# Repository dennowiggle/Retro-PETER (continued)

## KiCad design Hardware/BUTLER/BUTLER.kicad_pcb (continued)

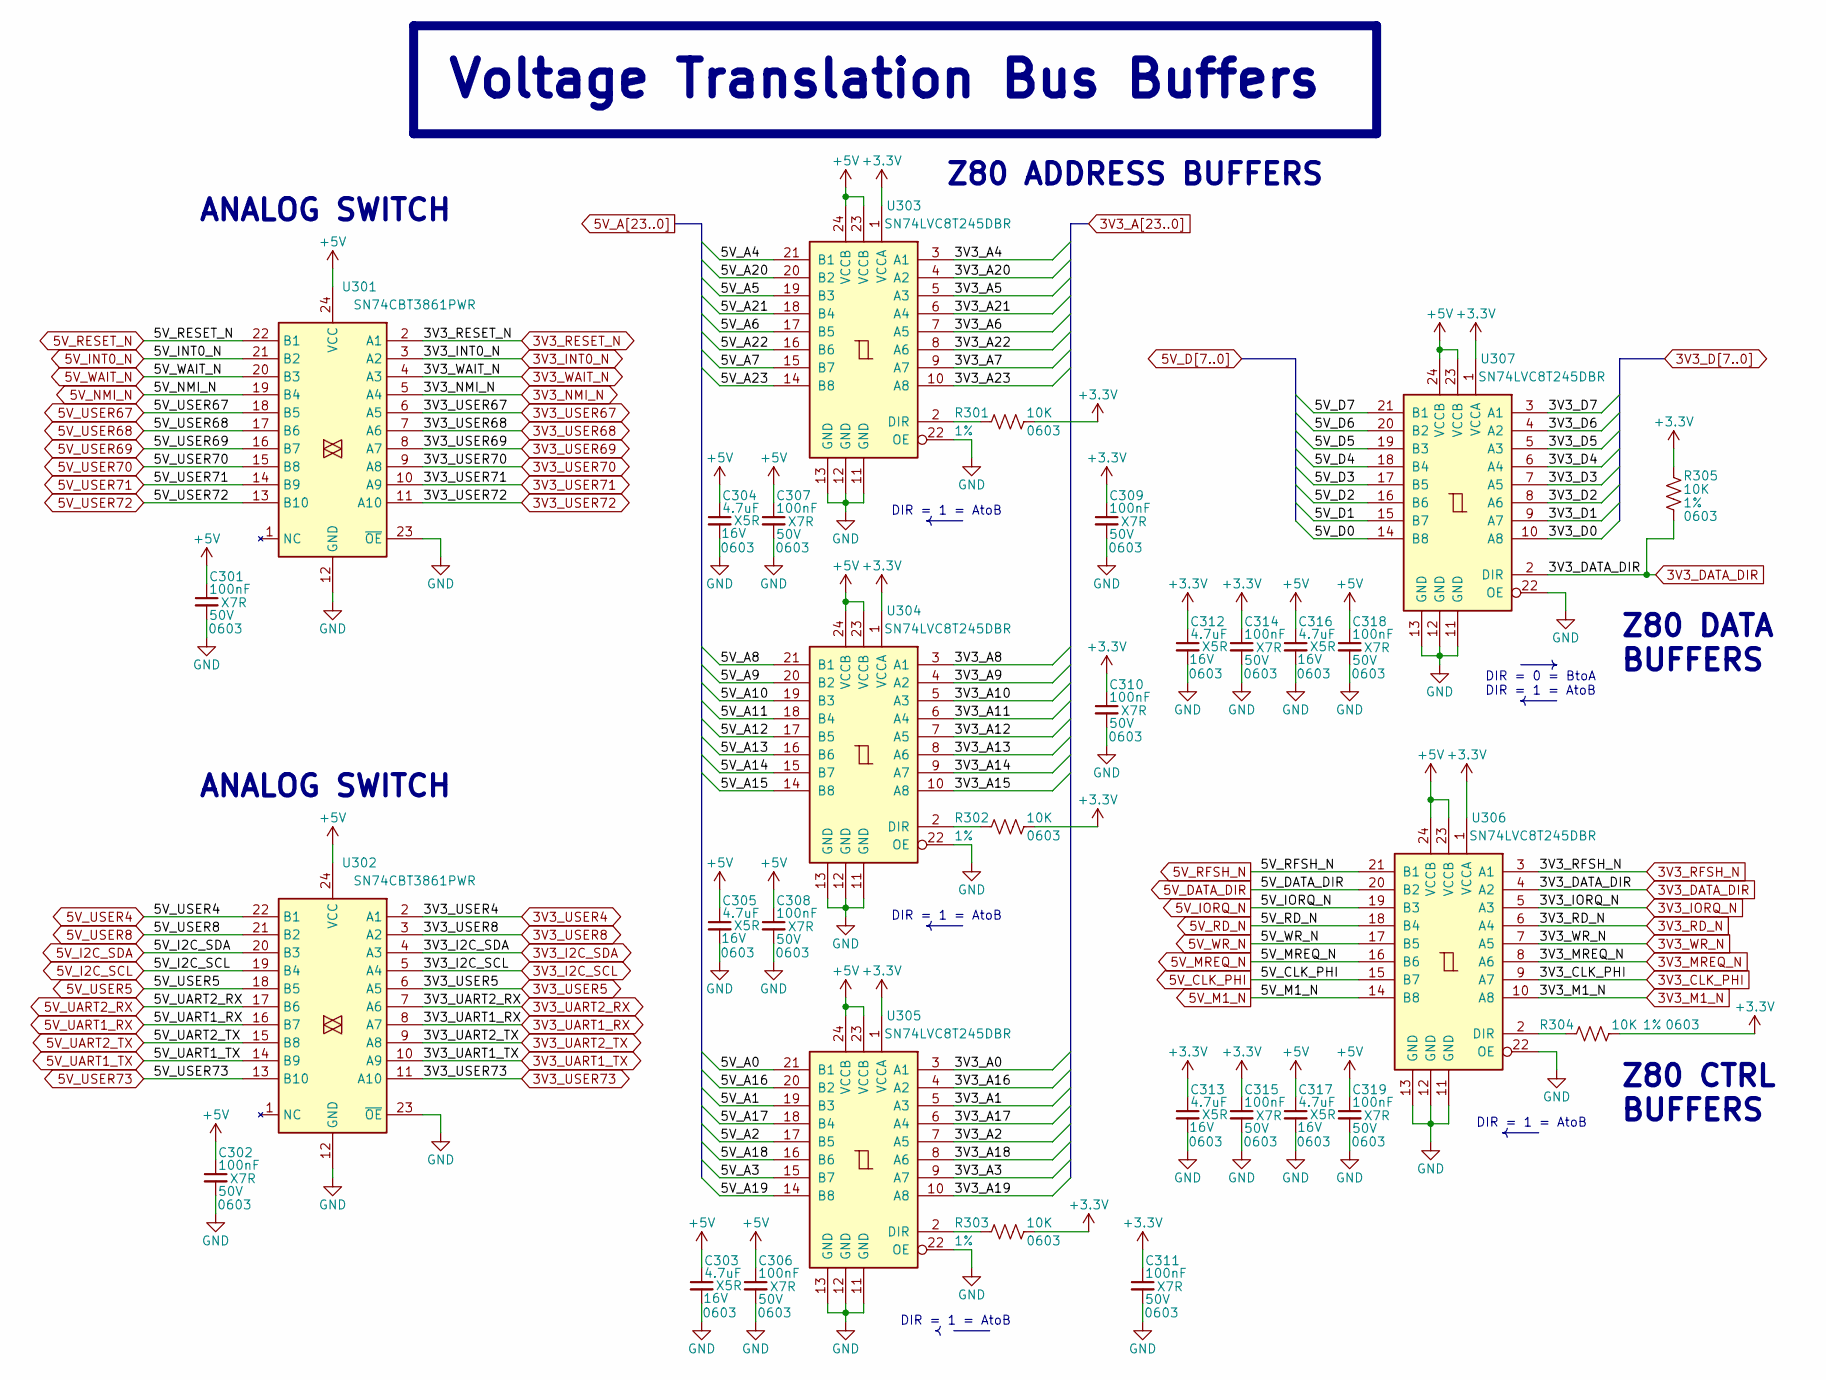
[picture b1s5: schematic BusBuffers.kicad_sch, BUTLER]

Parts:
C301, C302, C306, C307, C308, C309, C310, C311, C314, C315, C318, C319: 100nF; C_0603_1608Metric; Voltage 50V; Tolerance 10%; MPN CC0603KRX7R9BB104; Digikey 311-1344-1-ND
C303, C304, C305, C312, C313, C316, C317: 4.7uF; C_0603_1608Metric; Voltage 16V; Tolerance 10%; MPN CL10A475KO8NNNC; Digikey 1276-1784-1-ND
R301, R302, R303, R304, R305: 10K; R_0603_1608Metric; Tolerance 1%; MPN RC0603FR-0710KL; Digikey 311-10.0KHRCT-ND
U301, U302: SN74CBT3861PWR; TSSOP-24_4.4x7.8mm_P0.65mm; MPN SN74CBTD3861DBQR; Digikey 296-6483-1-ND
U303, U304, U305, U306, U307: SN74LVC8T245DBR; SSOP-24_5.3x8.2mm_P0.65mm; MPN SN74LVC8T245DBR; Digikey 296-21065-1-ND

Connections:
3V3_A0: U305.3 (A1); also elsewhere on the board
3V3_A1: U305.5 (A3); also elsewhere on the board
3V3_A2: U305.7 (A5); also elsewhere on the board
3V3_A3: U305.9 (A7); also elsewhere on the board
3V3_A4: U303.3 (A1); also elsewhere on the board
3V3_A5: U303.5 (A3); also elsewhere on the board
3V3_A6: U303.7 (A5); also elsewhere on the board
3V3_A7: U303.9 (A7); also elsewhere on the board
3V3_A8: U304.3 (A1); also elsewhere on the board
3V3_A9: U304.4 (A2); also elsewhere on the board
3V3_A10: U304.5 (A3); also elsewhere on the board
3V3_A11: U304.6 (A4); also elsewhere on the board
3V3_A12: U304.7 (A5); also elsewhere on the board
3V3_A13: U304.8 (A6); also elsewhere on the board
3V3_A14: U304.9 (A7); also elsewhere on the board
3V3_A15: U304.10 (A8); also elsewhere on the board
3V3_A16: U305.4 (A2); also elsewhere on the board
3V3_A17: U305.6 (A4); also elsewhere on the board
3V3_A18: U305.8 (A6); also elsewhere on the board
3V3_A19: U305.10 (A8); also elsewhere on the board
3V3_A20: U303.4 (A2); also elsewhere on the board
3V3_A21: U303.6 (A4); also elsewhere on the board
3V3_A22: U303.8 (A6); also elsewhere on the board
3V3_A23: U303.10 (A8); also elsewhere on the board
3V3_CLK_PHI: U306.9 (A7); also elsewhere on the board
3V3_D0: U307.10 (A8); also elsewhere on the board
3V3_D1: U307.9 (A7); also elsewhere on the board
3V3_D2: U307.8 (A6); also elsewhere on the board
3V3_D3: U307.7 (A5); also elsewhere on the board
3V3_D4: U307.6 (A4); also elsewhere on the board
3V3_D5: U307.5 (A3); also elsewhere on the board
3V3_D6: U307.4 (A2); also elsewhere on the board
3V3_D7: U307.3 (A1); also elsewhere on the board
3V3_DATA_DIR: R305.2, U306.4 (A2), U307.2 (DIR); also elsewhere on the board
3V3_I2C_SCL: U302.5 (A4); also elsewhere on the board
3V3_I2C_SDA: U302.4 (A3); also elsewhere on the board
3V3_INT0_N: U301.3 (A2); also elsewhere on the board
3V3_IORQ_N: U306.5 (A3); also elsewhere on the board
3V3_M1_N: U306.10 (A8); also elsewhere on the board
3V3_MREQ_N: U306.8 (A6); also elsewhere on the board
3V3_NMI_N: U301.5 (A4); also elsewhere on the board
3V3_RD_N: U306.6 (A4); also elsewhere on the board
3V3_RESET_N: U301.2 (A1); also elsewhere on the board
3V3_RFSH_N: U306.3 (A1); also elsewhere on the board
3V3_UART1_RX: U302.8 (A7); also elsewhere on the board
3V3_UART1_TX: U302.10 (A9); also elsewhere on the board
3V3_UART2_RX: U302.7 (A6); also elsewhere on the board
3V3_UART2_TX: U302.9 (A8); also elsewhere on the board
3V3_USER4: U302.2 (A1); also elsewhere on the board
3V3_USER5: U302.6 (A5); also elsewhere on the board
3V3_USER8: U302.3 (A2); also elsewhere on the board
3V3_USER67: U301.6 (A5); also elsewhere on the board
3V3_USER68: U301.7 (A6); also elsewhere on the board
3V3_USER69: U301.8 (A7); also elsewhere on the board
3V3_USER70: U301.9 (A8); also elsewhere on the board
3V3_USER71: U301.10 (A9); also elsewhere on the board
3V3_USER72: U301.11 (A10); also elsewhere on the board
3V3_USER73: U302.11 (A10); also elsewhere on the board
3V3_WAIT_N: U301.4 (A3); also elsewhere on the board
3V3_WR_N: U306.7 (A5); also elsewhere on the board
5V_A0: U305.21 (B1); also elsewhere on the board
5V_A1: U305.19 (B3); also elsewhere on the board
5V_A2: U305.17 (B5); also elsewhere on the board
5V_A3: U305.15 (B7); also elsewhere on the board
5V_A4: U303.21 (B1); also elsewhere on the board
5V_A5: U303.19 (B3); also elsewhere on the board
5V_A6: U303.17 (B5); also elsewhere on the board
5V_A7: U303.15 (B7); also elsewhere on the board
5V_A8: U304.21 (B1); also elsewhere on the board
5V_A9: U304.20 (B2); also elsewhere on the board
5V_A10: U304.19 (B3); also elsewhere on the board
5V_A11: U304.18 (B4); also elsewhere on the board
5V_A12: U304.17 (B5); also elsewhere on the board
5V_A13: U304.16 (B6); also elsewhere on the board
5V_A14: U304.15 (B7); also elsewhere on the board
5V_A15: U304.14 (B8); also elsewhere on the board
5V_A16: U305.20 (B2); also elsewhere on the board
5V_A17: U305.18 (B4); also elsewhere on the board
5V_A18: U305.16 (B6); also elsewhere on the board
5V_A19: U305.14 (B8); also elsewhere on the board
5V_A20: U303.20 (B2); also elsewhere on the board
5V_A21: U303.18 (B4); also elsewhere on the board
5V_A22: U303.16 (B6); also elsewhere on the board
5V_A23: U303.14 (B8); also elsewhere on the board
5V_CLK_PHI: U306.15 (B7); also elsewhere on the board
5V_D0: U307.14 (B8); also elsewhere on the board
5V_D1: U307.15 (B7); also elsewhere on the board
5V_D2: U307.16 (B6); also elsewhere on the board
5V_D3: U307.17 (B5); also elsewhere on the board
5V_D4: U307.18 (B4); also elsewhere on the board
5V_D5: U307.19 (B3); also elsewhere on the board
5V_D6: U307.20 (B2); also elsewhere on the board
5V_D7: U307.21 (B1); also elsewhere on the board
5V_DATA_DIR: U306.20 (B2); also elsewhere on the board
5V_I2C_SCL: U302.19 (B4); also elsewhere on the board
5V_I2C_SDA: U302.20 (B3); also elsewhere on the board
5V_INT0_N: U301.21 (B2); also elsewhere on the board
5V_IORQ_N: U306.19 (B3); also elsewhere on the board
5V_M1_N: U306.14 (B8); also elsewhere on the board
5V_MREQ_N: U306.16 (B6); also elsewhere on the board
5V_NMI_N: U301.19 (B4); also elsewhere on the board
5V_RD_N: U306.18 (B4); also elsewhere on the board
5V_RESET_N: U301.22 (B1); also elsewhere on the board
5V_RFSH_N: U306.21 (B1); also elsewhere on the board
5V_UART1_RX: U302.16 (B7); also elsewhere on the board
5V_UART1_TX: U302.14 (B9); also elsewhere on the board
5V_UART2_RX: U302.17 (B6); also elsewhere on the board
5V_UART2_TX: U302.15 (B8); also elsewhere on the board
5V_USER4: U302.22 (B1); also elsewhere on the board
5V_USER5: U302.18 (B5); also elsewhere on the board
5V_USER8: U302.21 (B2); also elsewhere on the board
5V_USER67: U301.18 (B5); also elsewhere on the board
5V_USER68: U301.17 (B6); also elsewhere on the board
5V_USER69: U301.16 (B7); also elsewhere on the board
5V_USER70: U301.15 (B8); also elsewhere on the board
5V_USER71: U301.14 (B9); also elsewhere on the board
5V_USER72: U301.13 (B10); also elsewhere on the board
5V_USER73: U302.13 (B10); also elsewhere on the board
5V_WAIT_N: U301.20 (B3); also elsewhere on the board
5V_WR_N: U306.17 (B5); also elsewhere on the board
+3.3V: C309.1, C310.1, C311.1, C312.1, C313.1, C314.1, C315.1, R301.2, R302.2, R303.2, R304.2, R305.1, U303.1 (VCCA), U304.1 (VCCA), U305.1 (VCCA), U306.1 (VCCA), U307.1 (VCCA); also elsewhere on the board
+5V: C301.1, C302.1, C303.1, C304.1, C305.1, C306.1, C307.1, C308.1, C316.1, C317.1, C318.1, C319.1, U301.24 (VCC), U302.24 (VCC), U303.23 (VCCB), U303.24 (VCCB), U304.23 (VCCB), U304.24 (VCCB), U305.23 (VCCB), U305.24 (VCCB), U306.23 (VCCB), U306.24 (VCCB), U307.23 (VCCB), U307.24 (VCCB); also elsewhere on the board
GND: C301.2, C302.2, C303.2, C304.2, C305.2, C306.2, C307.2, C308.2, C309.2, C310.2, C311.2, C312.2, C313.2, C314.2, C315.2, C316.2, C317.2, C318.2, C319.2, U301.12 (GND), U301.23 (~OE), U302.12 (GND), U302.23 (~OE), U303.11 (GND), U303.12 (GND), U303.13 (GND), U303.22 (OE), U304.11 (GND), U304.12 (GND), U304.13 (GND), U304.22 (OE), U305.11 (GND), U305.12 (GND), U305.13 (GND), U305.22 (OE), U306.11 (GND), U306.12 (GND), U306.13 (GND), U306.22 (OE), U307.11 (GND), U307.12 (GND), U307.13 (GND), U307.22 (OE); also elsewhere on the board
unnamed: R301.1, U303.2 (DIR)
unnamed: R302.1, U304.2 (DIR)
unnamed: R303.1, U305.2 (DIR)
unnamed: R304.1, U306.2 (DIR)

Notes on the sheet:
DIR = 1 = AtoB
DIR = 0 = BtoA
Z80 DATA BUFFERS
ANALOG SWITCH
Z80 ADDRESS BUFFERS
Z80 CTRL BUFFERS
Voltage Translation Bus Buffers

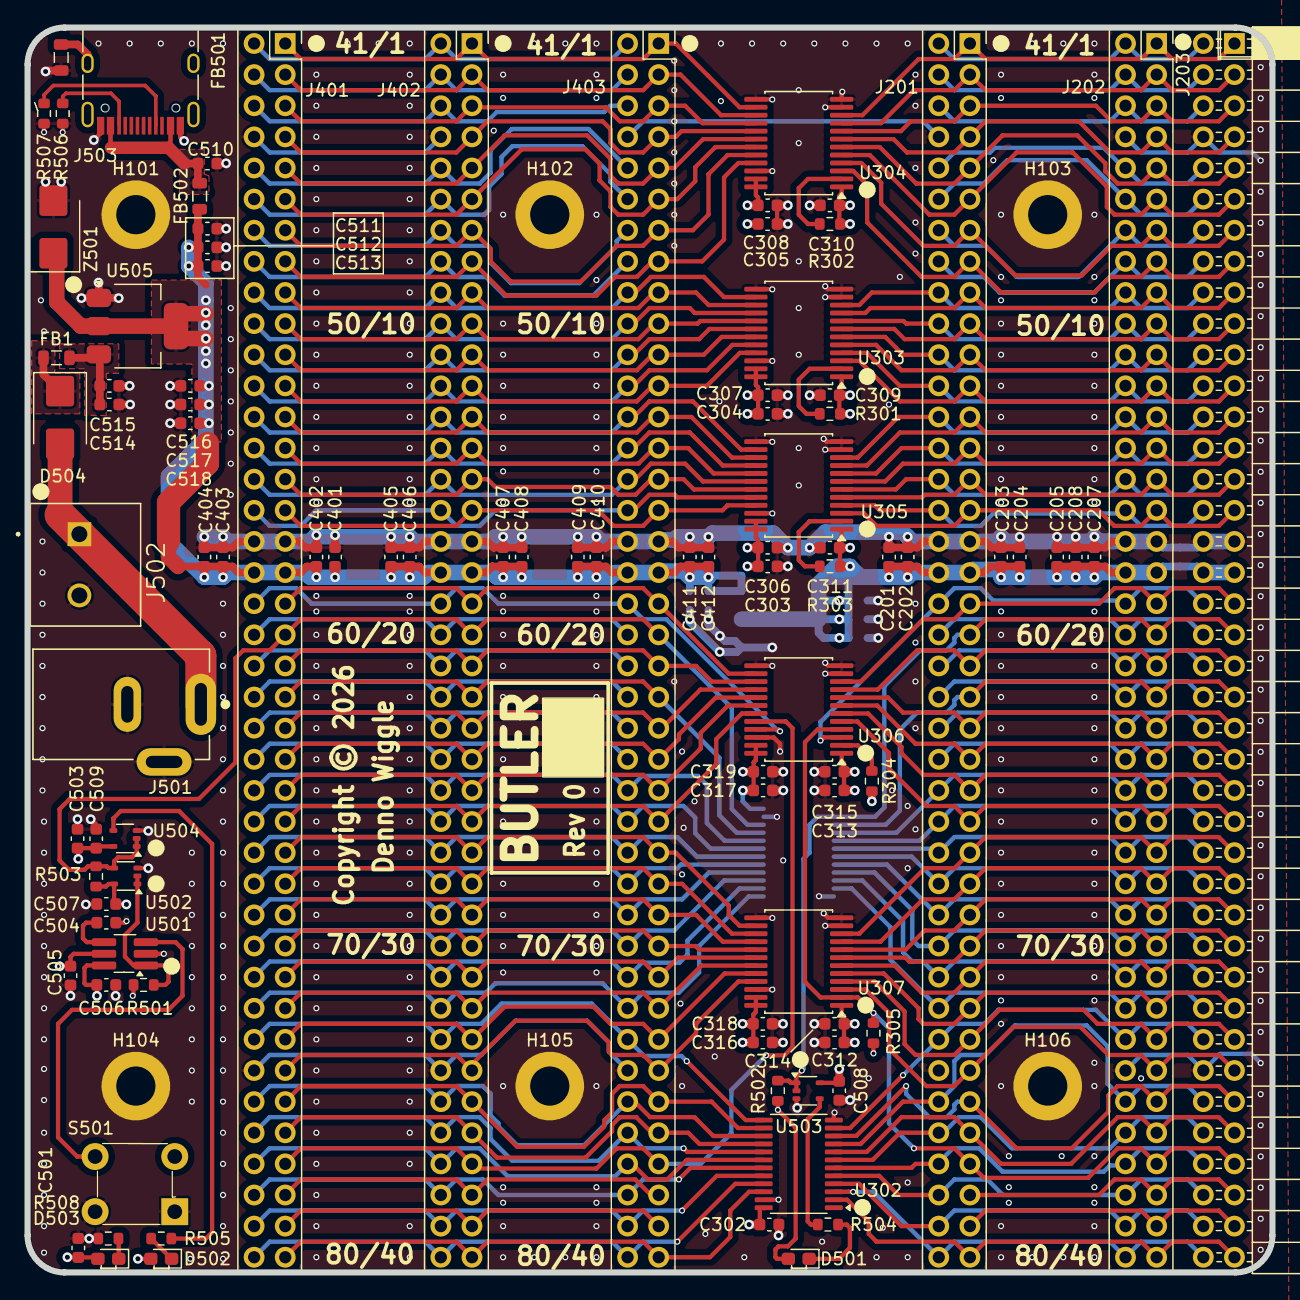
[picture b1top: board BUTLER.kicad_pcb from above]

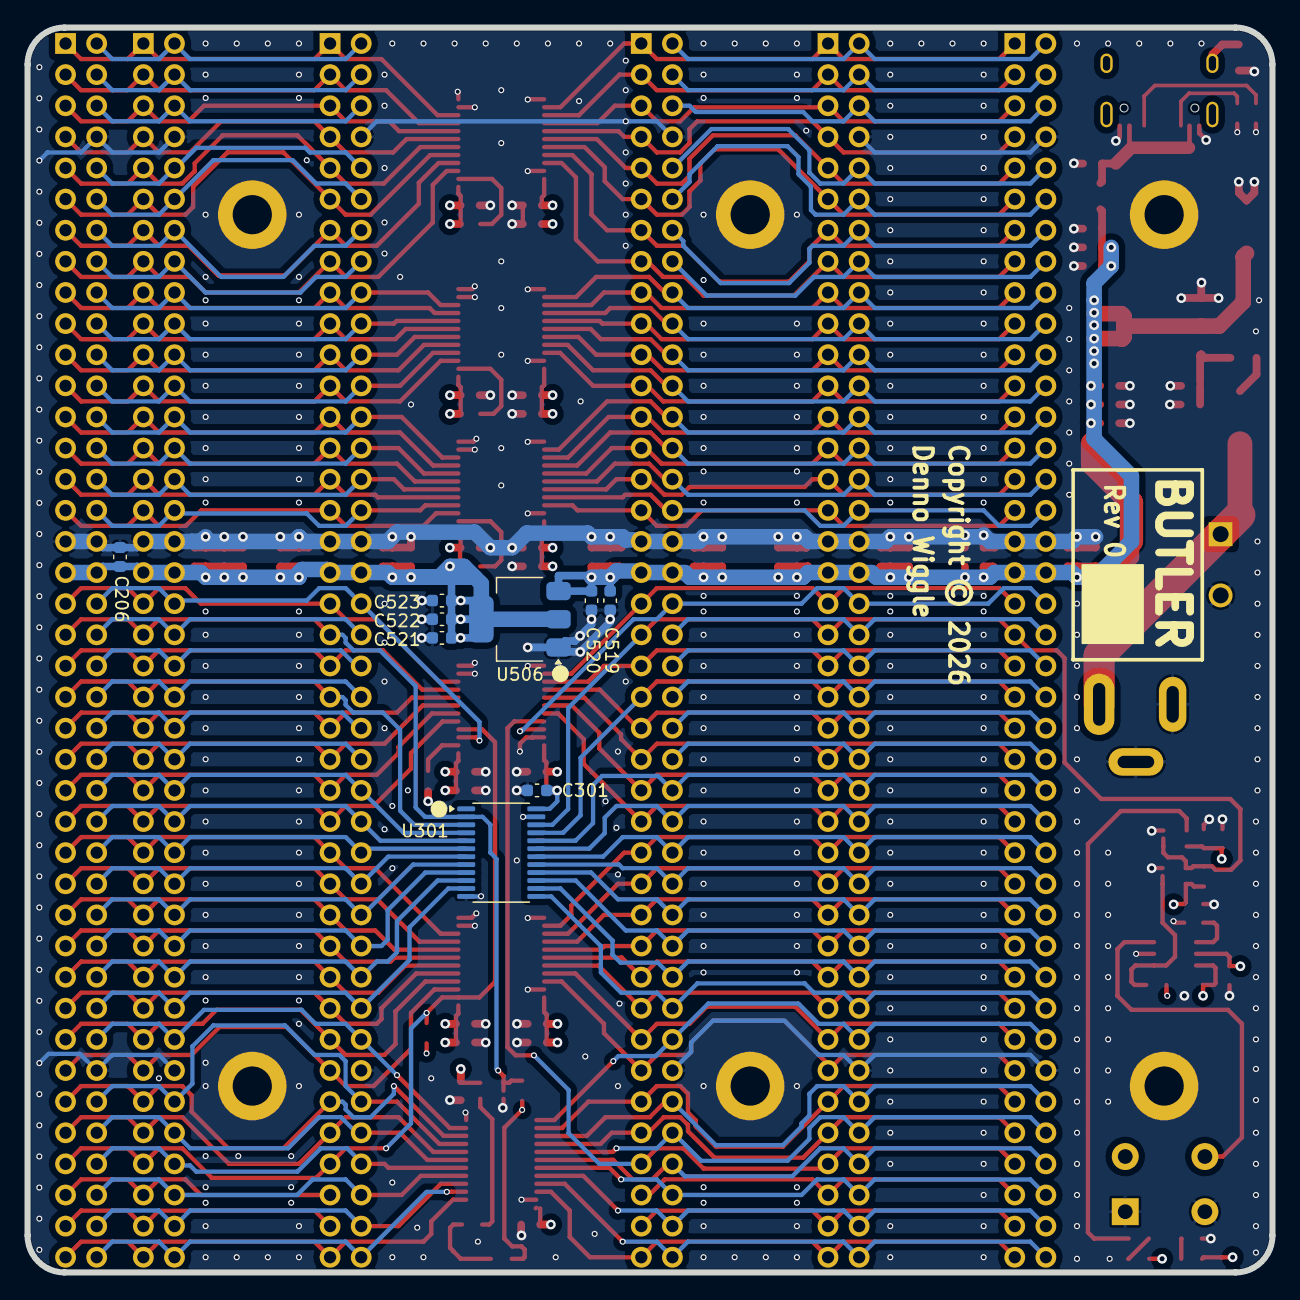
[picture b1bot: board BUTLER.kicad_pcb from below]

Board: 4 copper layers, 101.6 x 101.6 mm, 111 parts (9 on the bottom side), 170 nets.

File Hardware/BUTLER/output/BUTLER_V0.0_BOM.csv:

Reference,Value,Footprint,Qty,DNP,Digikey,LCSC Part #,MPN,Manufacturer,Voltage,Description
"C202,C203,C206,C207,C301,C302,C306,C307,C308,C309,C310,C311,C314,C315,C318,C319,C402,C403,C406,C407,C410,C411,C505,C506,C507,C508,C509,C510,C511,C515,C516",100nF,Capacitor_SMD:C_0603_1608Metric,31,,311-1344-1-ND,C14663,CC0603KRX7R9BB104,YAGEO,50V,CAP CER 0.1UF 50V X7R 0603
"C504,C520,C521",100nF,Capacitor_SMD:C_0603_1608Metric,3,DNP,311-1344-1-ND,C14663,CC0603KRX7R9BB104,YAGEO,50V,CAP CER 0.1UF 50V X7R 0603
"C201,C204,C205,C208,C303,C304,C305,C312,C313,C316,C317,C401,C404,C405,C408,C409,C412,C501,C503,C512,C513,C514,C517,C518",4.7uF,Capacitor_SMD:C_0603_1608Metric,24,,1276-1784-1-ND,C19666,CL10A475KO8NNNC,Yaego,16V,CAP CER 4.7UF 16V X5R 0603
"C519,C522,C523",4.7uF,Capacitor_SMD:C_0603_1608Metric,3,DNP,1276-1784-1-ND,C19666,CL10A475KO8NNNC,Yaego,16V,CAP CER 4.7UF 16V X5R 0603
"R301,R302,R303,R304,R305,R501,R502,R503",10K,Resistor_SMD:R_0603_1608Metric,8,,311-10.0KHRCT-ND,C98220,RC0603FR-0710KL,Yaego,,RES 10K OHM 1% 1/10W 0603
S501,1825910-6,digikey-footprints:Switch_Tactile_THT_6x6mm,1,,450-1650-ND,,1825910-6,TE Connectivity ALCOSWITCH Switches,,SWITCH TACTILE SPST-NO 0.05A 24V
R504,1K00,Resistor_SMD:R_0603_1608Metric,1,,311-1.00KHRCT-ND,C22548,RC0603FR-071KL,Yaego,,RES 1K OHM 1% 1/10W 0603
"R505,R508",2K32,Resistor_SMD:R_0603_1608Metric,2,,311-2.32KHRCT-ND,C137749,RC0603FR-072K32L,Yaego,,RES 2K32 OHM 1% 1/10W 0603
"R506,R507",5K1,Resistor_SMD:R_0603_1608Metric,2,,311-5.10KHRCT-ND,C105580,RC0603FR-075K1L,Yaego,,RES 5.1K OHM 1% 1/10W 0603
U502,"74AHC1G09GW,125",Package_TO_SOT_SMD:SOT-353_SC-70-5,1,,1727-6017-1-ND,C730245,"74AHC1G09GW,125",Nexperia USA Inc.,,IC GATE AND 1CH 2-INP OPEN DRAIN 5TSSOP
"U503,U504","74LVC1G38GW,125",Package_TO_SOT_SMD:SOT-353_SC-70-5,2,,1727-6077-1-ND,C548373,"74LVC1G38GW,125",Nexperia USA Inc.,,IC GATE NAND 1CH 2-INP OPEN DRAIN 5TSSOP
U505,AZ1117CH-5.0TRG1,Package_TO_SOT_SMD:SOT-223,1,,AZ1117CH-5.0TRG1DICT-ND,C99342,AZ1117CH-5.0TRG1,Diodes Inc,,IC REG LINEAR 5.0V 1A SOT223
D504,B320B-13-F,Diode_SMD:D_SMB,1,,B320B-FDICT-ND,C134449,B320B-13-F,Diodes Inc,,DIODE SCHOTTKY 20V 3A SMB
"FB1,FB501,FB502",BLM21PG121SN1D,Inductor_SMD:L_0805_2012Metric,3,,490-5986-1-ND,C79382,BLM21PG121SN1D,Murata Electronics North America,,FERRITE BEAD 120 OHM 0805 3A
"J201,J202,J401,J402,J403",Conn_02x40_Top_Bottom,"WTM_Library:PinSocket_2x40_P2.54mm_Horizontal_RCBUS80,WTM_Library:PinSocket_2x40_P2.54mm_Vertical_RCBUS80",5,,,C7500806,,,,"CONN RCPT 80POS 0.1 TIN PCB R/A,Generic connector, double row, 02x40, top/bottom pin numbering scheme (row 1: 1...pins_per_row, row2: pins_per_row+1 ... num_pins), script generated (kicad-library-utils/schlib/autogen/connector/)"
J203,Conn_02x40_Top_Bottom,"WTM_Library:PinSocket_2x40_P2.54mm_Horizontal_RCBUS80,WTM_Library:PinSocket_2x40_P2.54mm_Vertical_RCBUS80",1,,612-SSW-140-02-T-D-RA-ND,C22385332,SSW-140-02-T-D-RA,Samtec Inc.,,"CONN RCPT 80POS 0.1 TIN PCB R/A,Generic connector, double row, 02x40, top/bottom pin numbering scheme (row 1: 1...pins_per_row, row2: pins_per_row+1 ... num_pins), script generated (kicad-library-utils/schlib/autogen/connector/)"
"D501,D502,D503",LED_LTST-S270KGKT,WTM_Library:LTST-S270KGKT,3,,160-1478-1-ND,C125113,LTST-S270KGKT,Lite-On Inc.,,LED 571NM GREEN CLEAR CHIP 0603 R/A
J501,PJ-002A,WTM_Library:CUI_PJ-002A,1,,CP-002A-ND,,PJ-002A,,,CONN PWR JACK 2X5.5MM SOLDER
J502,Screw_Terminal_01x02,WTM_Library:CUI_TB001-500-02BE,1,,102-6134-ND,,TB001-500-02BE,CUI Devices,,"TERM BLOCK, SCREW TYPE, 5.00MM PCB"
Z501,SMBJ5.0A,Diode_SMD:D_SMB,1,,SMBJ5.0ALFCT-ND,C110528,SMBJ5.0A,Littlefuse,,TVS DIODE 5VWM 9.2VC DO214AA
"U301,U302",SN74CBT3861PWR,Package_SO:TSSOP-24_4.4x7.8mm_P0.65mm,2,,296-6483-1-ND,C44508,SN74CBTD3861DBQR,Texas Instruments,,10-bit FET bus switch
"U303,U304,U305,U306,U307",SN74LVC8T245DBR,Package_SO:SSOP-24_5.3x8.2mm_P0.65mm,5,,296-21065-1-ND,C19197,SN74LVC8T245DBR,Texas Instruments,,IC TRANSLATION TXRX 5.5V 24SSOP
U506,TLV1117LV33DCYR,Package_TO_SOT_SMD:SOT-223,1,DNP,296-28778-1-ND,C15578,TLV1117LV33DCYR,Texas Instruments,,IC REG LINEAR 3.3V 1A SOT223-4
U501,TPS3808EG50DBVR,Package_TO_SOT_SMD:TSOT-23-6_HandSoldering,1,,296-TPS3808EG50DBVRCT-ND,C134123,TPS3808EG50DBVR,Texas Instruments,,IC VOLT SUPERVISOR 5V SOT23-6
J503,USB_C_Receptacle_USB2.0,WTM_Library:USB_C_Receptacle_HRO_TYPE-C-31-M-12,1,,2073-USB4105-GF-ACT-ND,C167321,USB4105-GF-A,GCT,,CONN RCP USB2.0 TYP C 24P SMD RA

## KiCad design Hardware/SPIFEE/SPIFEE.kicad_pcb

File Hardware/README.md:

# Retro-PETER Hardware Design Files
A Retro Computer project => FPGA peripheral board + 3.3V RCBUS slot + CPU board(s) making a custom system.

Hardware design files in KiCad 8 format are located here. 

Schematic design PDF drawings can be found in the `output` sub-directory of each board directory.

**Warning** : This is a 3.3V system and any connections to PETER, including RCBUS, must NOT exceed 3.3V.

**Disclaimer** : This is a hobby project and a vehicle for play. Not intended to be a product or to be optimised for size, cost, function, or meet any standard. All boards are prototypes and should be considered such even if there are new revisions over time.

## Description
Retro-PETER is a family of boards based around the Lattice ECP5 FPGA to create a custom retro computer system.
* [PETER](PETER "Peripheral ECP5 Technology and Entertainment Resource board.") base board with FPGA provides the peripheral features. It has on board SRAM memory but no CPU.
    - One 3.3V RCBUS connector provides a CPU slot.
    - One 3.3V RCBUS expansion connector allows connection of an RCBUS backplane for more card slots.
* [ANALYZER](Analyzer "Logic Analyzer for RCBUS using PI PICO 2") is a 5V tolerant 72 channel logic analyzer for RCBUS.
* [BALD](BALD "Bus Activity LED Display.") is an RCBUS LED card that flickers lights when there is activity. I found this useful for bringup of new CPU's either on an RCBUS CPU card or internal CPU cores.
* [BUTLER](BUTLER "Backplane with Universal Translation Logic for Exploring Retro") is a backplane with voltage translation logic to support 2 x 3.3V connectors for 3.3V RCBUS cards and 3 x 5V connectors for 5V RCBUS cards.
* [GOLD](GOLD "GPIO On LED Display.") is a simple LED board that connects to 6 GPIO outputs for flashing lights and debug info. I love a binary counter.
* [RANDY](RANDY "RCBUS Adapter to Nouveau Design. Yeah!") is a bus adapter from RCBUS to John's Basement [2067-Z8S180](https://github.com/johnwinans/2067-Z8S180/) card.
* [SEWER](SEWER "Simple Eval With EZ80F91 on RCBUS") is an eZ80 CPU card.
* [SPIFEE](SPIFEE "Sixty-eight thousand Processor Including Flash Engineering Eval") is an RCBUS board with an M68SEC000FU20 CPU that runs in 8-bit mode.
* [ZORO](ZORO "Z8S180 On RCBUS Only.") is a Z180 RCBUS CPU card.

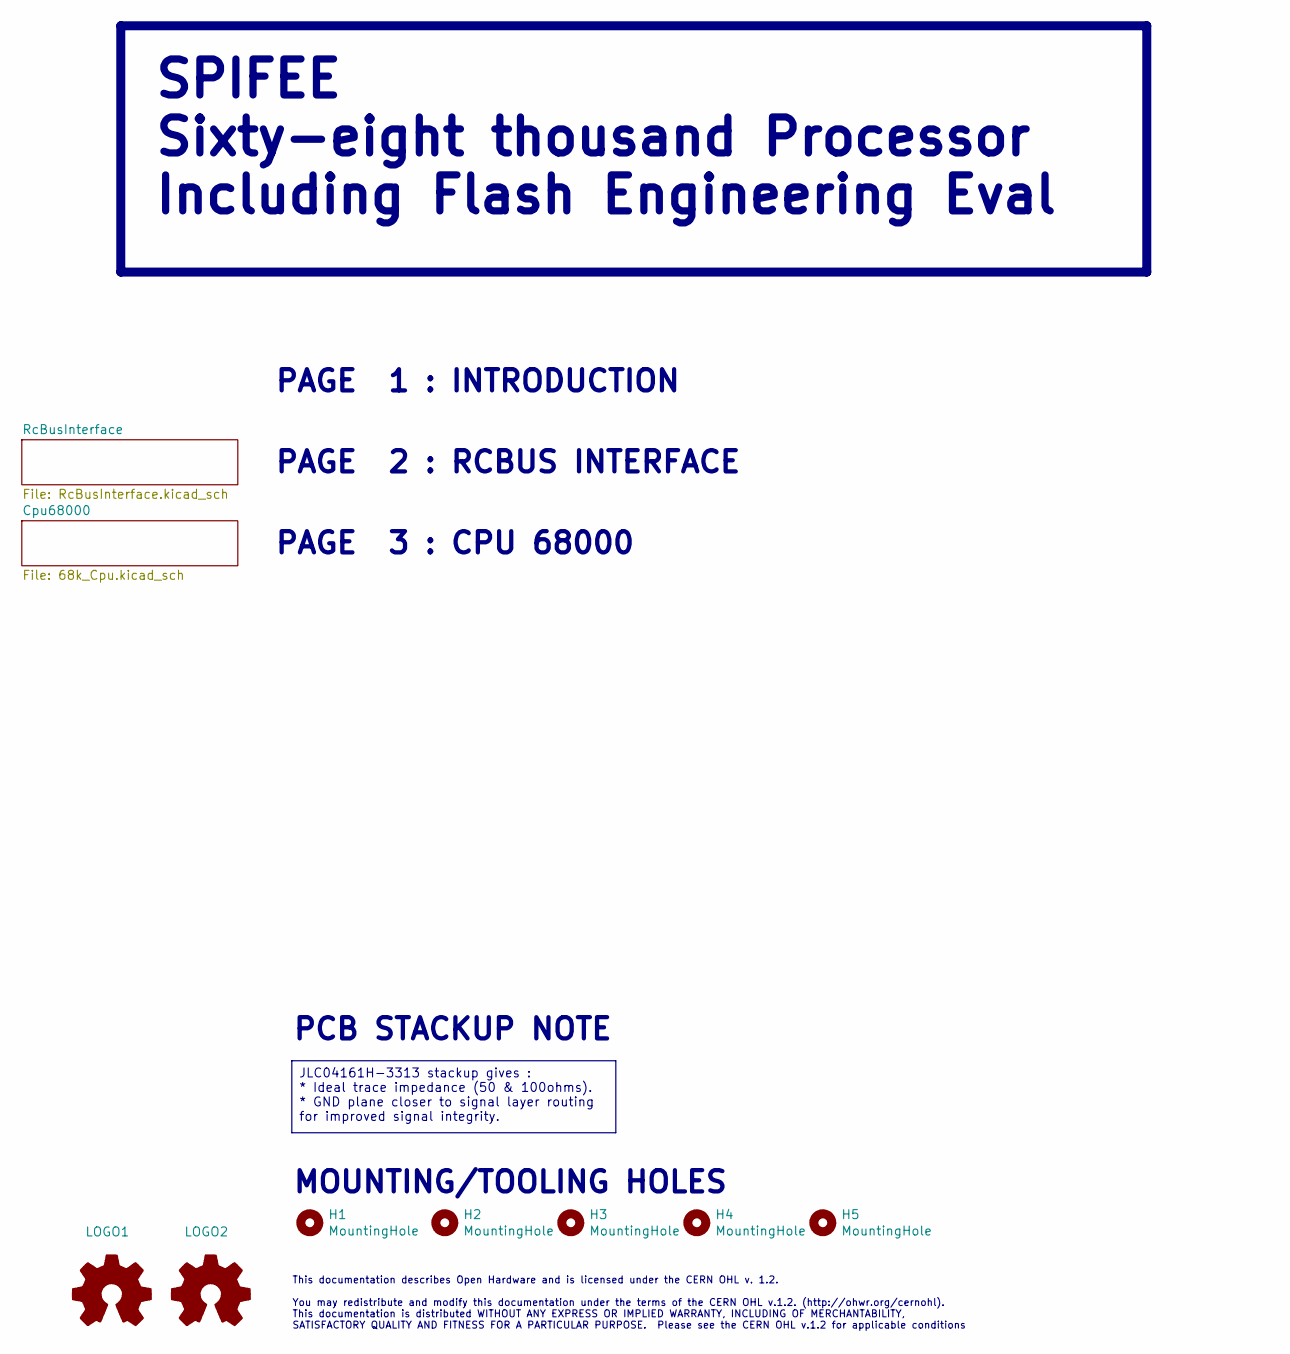
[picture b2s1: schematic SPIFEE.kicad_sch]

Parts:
H1: MountingHole; MountingHole_3.2mm_M3
H2, H3, H4, H5: MountingHole; MountingHole_2.7mm_M2.5_DIN965
LOGO1, LOGO2: Logo_Open_Hardware_Small; OSHW-Logo_7.5x8mm_SilkScreen

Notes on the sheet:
MOUNTING/TOOLING HOLES
PAGE 1 : INTRODUCTION
PCB STACKUP NOTE
This documentation describes Open Hardware and is licensed under the CERN OHL v. 1.2. You may redistribute and modify this documentation under the terms of the CERN OHL v.1.2. (http://ohwr.org/cernohl). This documentation is distributed WITHOUT ANY EXPRESS OR IMPLIED WARRANTY, INCLUDING OF MERCHANT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
PAGE 3 : CPU 68000
PAGE 2 : RCBUS INTERFACE
JLC04161H-3313 stackup gives : * Ideal trace impedance (50 & 100ohms). * GND plane closer to signal layer routing for improved signal integrity.
SPIFEE Sixty-eight thousand Processor Including Flash Engineering Eval

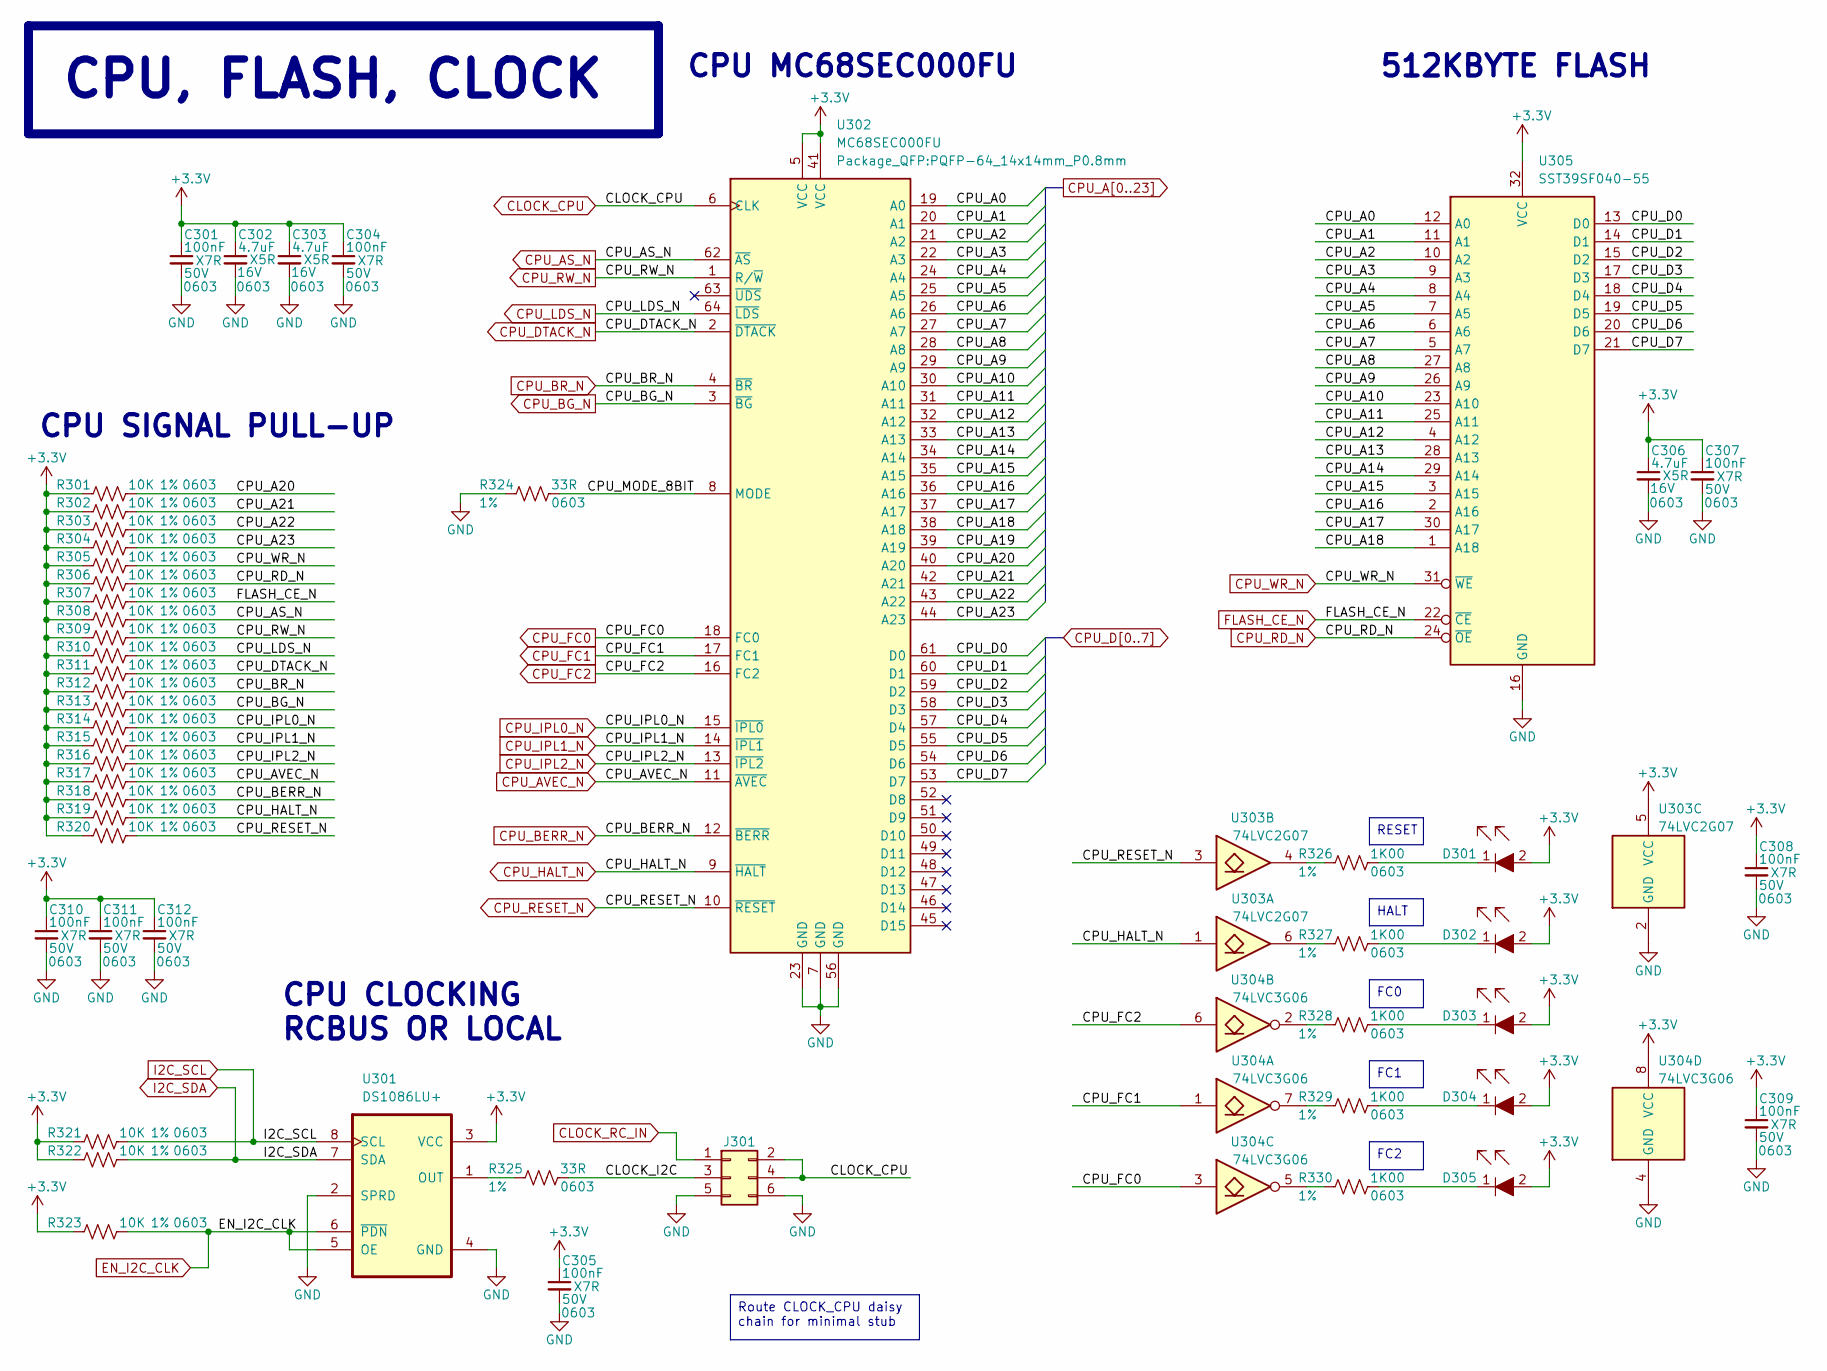
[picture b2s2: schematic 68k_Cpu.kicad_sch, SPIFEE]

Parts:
C301, C304, C305, C307, C308, C309, C310, C311, C312: 100nF; C_0603_1608Metric; Voltage 50V; Tolerance 10%; MPN CC0603KRX7R9BB104; Digikey 311-1344-1-ND
C302, C303, C306: 4.7uF; C_0603_1608Metric; Voltage 16V; Tolerance 10%; MPN CL10A475KO8NNNC; Digikey 1276-1784-1-ND
D301, D302, D303, D304, D305: LED_LTST-S270KGKT; LTST-S270KGKT; MPN LTST-S270KGKT; Digikey 160-1478-1-ND
J301: Conn_02x03; PinHeader_2x03_P2.54mm_Vertical; MPN PH2-06-UA; Digikey 2057-PH2-06-UA-ND
R301, R302, R303, R304, R305, R306, R307, R308, R309, R310, R311, R312, R313, R314, R315, R316, R317, R318, R319, R320, R321, R322, R323: 10K; R_0603_1608Metric; Tolerance 1%; MPN RC0603FR-0710KL; Digikey 311-10.0KHRCT-ND
R324, R325: 33R; R_0603_1608Metric; Tolerance 1%; MPN RC0603FR-0733RL; Digikey 13-RC0603FR-0733RLCT-ND
R326, R327, R328, R329, R330: 1K00; R_0603_1608Metric; Tolerance 1%; MPN RC0603FR-071KL; Digikey 311-1.00KHRCT-ND
U301: DS1086LU+; MSOP-8_3x3mm_P0.65mm; MPN DS1086LU+; Digikey DS1086LU+-ND
U302: MC68SEC000FU; PQFP-64_14x14mm_P0.8mm; MPN MC68SEC000FU20
U303: 74LVC2G07; SOT-363_SC-70-6; MPN 74LVC2G07GW,125; Digikey 1727-4121-1-ND
U304: 74LVC3G06; SSOP-8_2.95x2.8mm_P0.65mm; MPN 74LVC3G06SS8-7; Digikey 31-74LVC3G06SS8-7CT-ND
U305: SST39SF040-55; PLCC32_SMT_SOCKET_AMPHENOL_69802-132LF; MPN SST39LF040-55-4C-NHE; Digikey SST39LF040-55-4C-NHE-ND

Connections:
+3.3V: C301.1, C302.1, C303.1, C304.1, C305.1, C306.1, C307.1, C308.1, C309.1, C310.1, C311.1, C312.1, D301.2, D302.2, D303.2, D304.2, D305.2, R301.1, R302.1, R303.1, R304.1, R305.1, R306.1, R307.1, R308.1, R309.1, R310.1, R311.1, R312.1, R313.1, R314.1, R315.1, R316.1, R317.1, R318.1, R319.1, R320.1, R321.1, R322.1, R323.1, U301.3 (VCC), U302.5 (VCC), U302.41 (VCC), U303.5 (VCC), U304.8 (VCC), U305.32 (VCC); also elsewhere on the board
/Cpu68000/CLOCK_I2C: J301.3, R325.2
/Cpu68000/CPU_MODE_8BIT: R324.2, U302.8 (MODE)
CLOCK_CPU: J301.2, J301.4, U302.6 (CLK); also elsewhere on the board
CLOCK_RC_IN: J301.1; also elsewhere on the board
CPU_A0: U302.19 (A0), U305.12 (A0); also elsewhere on the board
CPU_A1: U302.20 (A1), U305.11 (A1); also elsewhere on the board
CPU_A2: U302.21 (A2), U305.10 (A2); also elsewhere on the board
CPU_A3: U302.22 (A3), U305.9 (A3); also elsewhere on the board
CPU_A4: U302.24 (A4), U305.8 (A4); also elsewhere on the board
CPU_A5: U302.25 (A5), U305.7 (A5); also elsewhere on the board
CPU_A6: U302.26 (A6), U305.6 (A6); also elsewhere on the board
CPU_A7: U302.27 (A7), U305.5 (A7); also elsewhere on the board
CPU_A8: U302.28 (A8), U305.27 (A8); also elsewhere on the board
CPU_A9: U302.29 (A9), U305.26 (A9); also elsewhere on the board
CPU_A10: U302.30 (A10), U305.23 (A10); also elsewhere on the board
CPU_A11: U302.31 (A11), U305.25 (A11); also elsewhere on the board
CPU_A12: U302.32 (A12), U305.4 (A12); also elsewhere on the board
CPU_A13: U302.33 (A13), U305.28 (A13); also elsewhere on the board
CPU_A14: U302.34 (A14), U305.29 (A14); also elsewhere on the board
CPU_A15: U302.35 (A15), U305.3 (A15); also elsewhere on the board
CPU_A16: U302.36 (A16), U305.2 (A16); also elsewhere on the board
CPU_A17: U302.37 (A17), U305.30 (A17); also elsewhere on the board
CPU_A18: U302.38 (A18), U305.1 (A18); also elsewhere on the board
CPU_A19: U302.39 (A19); also elsewhere on the board
CPU_A20: R301.2, U302.40 (A20); also elsewhere on the board
CPU_A21: R302.2, U302.42 (A21); also elsewhere on the board
CPU_A22: R303.2, U302.43 (A22); also elsewhere on the board
CPU_A23: R304.2, U302.44 (A23); also elsewhere on the board
CPU_AS_N: R308.2, U302.62 (~AS); also elsewhere on the board
CPU_AVEC_N: R317.2, U302.11 (~AVEC); also elsewhere on the board
CPU_BERR_N: R318.2, U302.12 (~BERR); also elsewhere on the board
CPU_BG_N: R313.2, U302.3 (~BG); also elsewhere on the board
CPU_BR_N: R312.2, U302.4 (~BR); also elsewhere on the board
CPU_D0: U302.61 (D0), U305.13 (D0); also elsewhere on the board
CPU_D1: U302.60 (D1), U305.14 (D1); also elsewhere on the board
CPU_D2: U302.59 (D2), U305.15 (D2); also elsewhere on the board
CPU_D3: U302.58 (D3), U305.17 (D3); also elsewhere on the board
CPU_D4: U302.57 (D4), U305.18 (D4); also elsewhere on the board
CPU_D5: U302.55 (D5), U305.19 (D5); also elsewhere on the board
CPU_D6: U302.54 (D6), U305.20 (D6); also elsewhere on the board
CPU_D7: U302.53 (D7), U305.21 (D7); also elsewhere on the board
CPU_DTACK_N: R311.2, U302.2 (~DTACK); also elsewhere on the board
CPU_FC0: U302.18 (FC0), U304.3; also elsewhere on the board
CPU_FC1: U302.17 (FC1), U304.1; also elsewhere on the board
CPU_FC2: U302.16 (FC2), U304.6; also elsewhere on the board
CPU_HALT_N: R319.2, U302.9 (~HALT), U303.1; also elsewhere on the board
CPU_IPL0_N: R314.2, U302.15 (~IPL0); also elsewhere on the board
CPU_IPL1_N: R315.2, U302.14 (~IPL1); also elsewhere on the board
CPU_IPL2_N: R316.2, U302.13 (~IPL2); also elsewhere on the board
CPU_LDS_N: R310.2, U302.64 (~LDS); also elsewhere on the board
CPU_RD_N: R306.2, U305.24 (~OE); also elsewhere on the board
CPU_RESET_N: R320.2, U302.10 (~RESET), U303.3; also elsewhere on the board
CPU_RW_N: R309.2, U302.1 (R/~W); also elsewhere on the board
CPU_WR_N: R305.2, U305.31 (~WE); also elsewhere on the board
EN_I2C_CLK: R323.2, U301.5 (OE), U301.6 (~PDN); also elsewhere on the board
FLASH_CE_N: R307.2, U305.22 (~CE); also elsewhere on the board
GND: C301.2, C302.2, C303.2, C304.2, C305.2, C306.2, C307.2, C308.2, C309.2, C310.2, C311.2, C312.2, J301.5, J301.6, R324.1, U301.2 (SPRD), U301.4 (GND), U302.7 (GND), U302.23 (GND), U302.56 (GND), U303.2 (GND), U304.4 (GND), U305.16 (GND); also elsewhere on the board
I2C_SCL: R321.2, U301.8 (SCL); also elsewhere on the board
I2C_SDA: R322.2, U301.7 (SDA); also elsewhere on the board
unnamed: D301.1, R326.2
unnamed: D302.1, R327.2
unnamed: D303.1, R328.2
unnamed: D304.1, R329.2
unnamed: D305.1, R330.2
unnamed: R326.1, U303.4
unnamed: R327.1, U303.6
unnamed: R328.1, U304.2
unnamed: R329.1, U304.7
unnamed: R330.1, U304.5
unnamed: R325.1, U301.1 (OUT)

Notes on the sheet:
512KBYTE FLASH
CPU SIGNAL PULL-UP
CPU CLOCKING RCBUS OR LOCAL
CPU MC68SEC000FU
HALT
FC0
CPU, FLASH, CLOCK
Route CLOCK_CPU daisy chain for minimal stub
FC1
RESET
FC2
